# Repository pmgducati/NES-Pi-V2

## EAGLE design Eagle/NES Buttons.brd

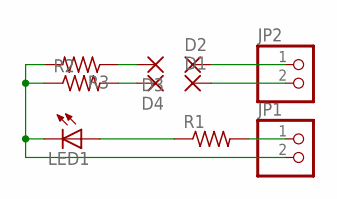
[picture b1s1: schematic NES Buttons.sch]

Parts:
D1, D2, D3, D4: 2,15/1,0
JP1, JP2: PINHD-1X2; 1X02
LED1: LED3MM
R1, R2, R3: R-US_R1206; R1206

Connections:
GND: JP1.2, LED1.K (C), R2.1, R3.2
unnamed: JP1.1, R1.2
unnamed: D3.1, R3.1
unnamed: D4.1, R2.2
unnamed: LED1.A, R1.1
unnamed: D1.1, JP2.2
unnamed: D2.1, JP2.1

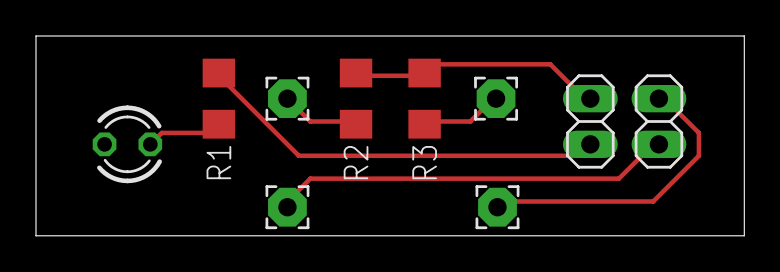
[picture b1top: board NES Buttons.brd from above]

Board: 2 copper layers, 39.4 x 11.1 mm, 10 parts (0 on the bottom side), 7 nets.

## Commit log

2016-10-03 :circus_tent: Added .gitattributes & .gitignore files
2016-10-03 Adding Eagles board files and Solidworks files (Case)
